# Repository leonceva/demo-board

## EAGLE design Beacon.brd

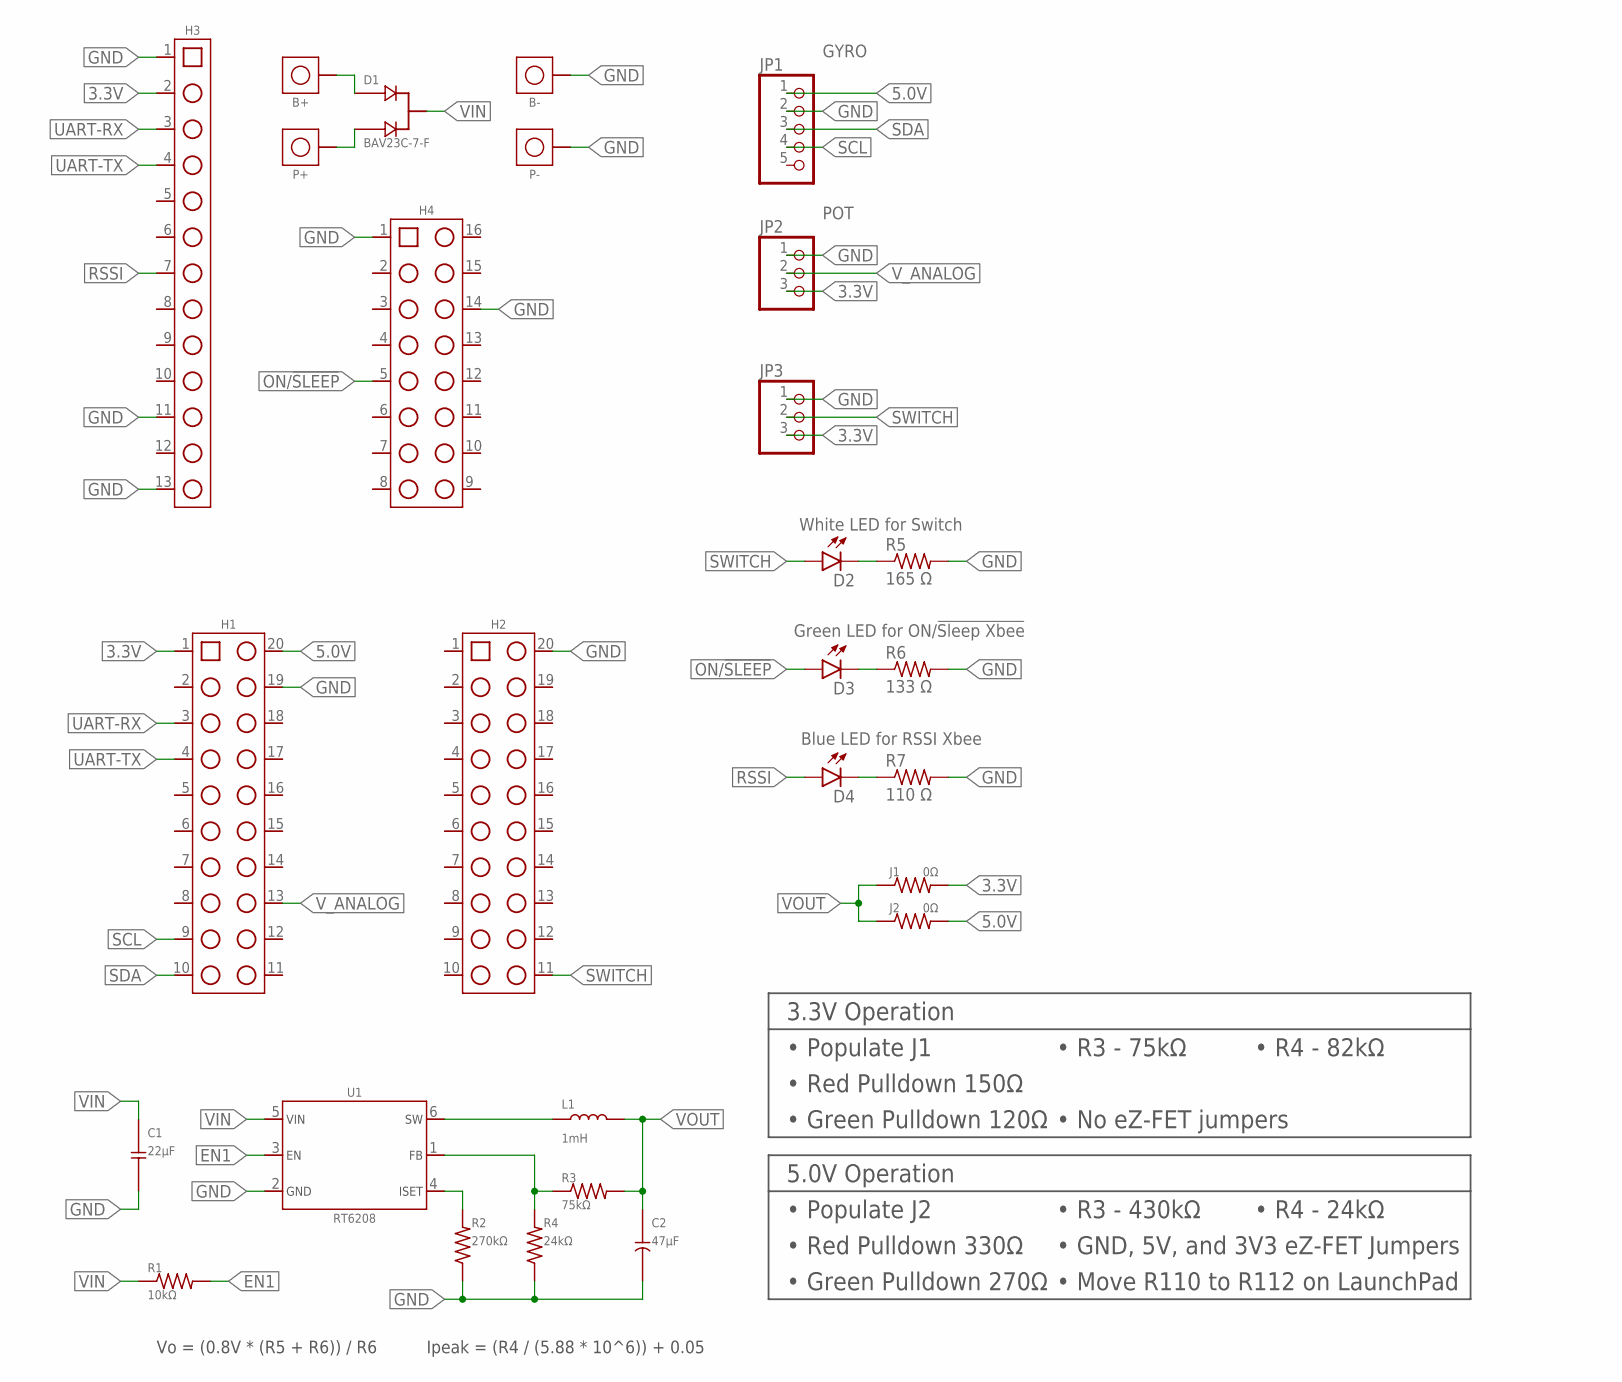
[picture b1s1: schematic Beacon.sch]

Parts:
B+: CON_HEADER-01WTB-24G; THT_WTB-24G
B-: CON_HEADER-01WTB-24G; THT_WTB-24G
C1: 22µF; SMT_1206
C2: 47µF; SMT_CAP-1206
D1: BAV23C-7-F; SMT_SOT23-3
D2, D3, D4: BEAGLEBONE_BLUE_LED-FKIT-1206; BEAGLEBONE_BLUE_BEAGLEBONE_BLUE_FKIT-LED-1206
H1, H2: CON_HEADER-20; CON_HEADER-0.1"-TH-2×10
H3: CON_HEADER-13SM-B; CON_HEADER-2MM-SM-1×13B
H4: CON_HEADER-16SM-B; CON_HEADER-2MM-SM-1×16B
J1, J2: 0Ω; SMT_0603
JP1: PINHD-1X5; 1X05
JP2, JP3: PINHD-1X3/90; 1X03/90
L1: 1mH; SMT_1210
P+: CON_HEADER-01WTB-24G; THT_WTB-24G
P-: CON_HEADER-01WTB-24G; THT_WTB-24G
R1: 10kΩ; SMT_0603
R2: 270kΩ; SMT_0603
R3: 75kΩ; SMT_0603
R4: 24kΩ; SMT_0603
R5: 165 Ω; RES_1206
R6: 133 Ω; RES_1206
R7: 110 Ω; RES_1206
U1: RT6208; SMT_SOT23-6

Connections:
3.3V: H1.1 (PIN_1), H3.2 (PIN_2), J1.2, JP2.3, JP3.3
5.0V: H1.20 (PIN_20), J2.2, JP1.1
EN1: R1.2, U1.3 (B)
FB: R3.1, R4.2, U1.1 (E)
GND: B-.1, C1.1, C2.2, H1.19 (PIN_19), H2.20 (PIN_20), H3.1 (PIN_1), H3.11 (PIN_11), H3.13 (PIN_13), H4.1 (PIN_1), H4.14 (PIN_14), JP1.2, JP2.1, JP3.1, P-.1, R2.1, R4.1, R5.2, R6.2, R7.2, U1.2 (C)
ISET: R2.2, U1.4 (D)
unnamed: D2.C, R5.1
unnamed: D3.C, R6.1
unnamed: D4.C, R7.1
unnamed: B+.1, D1.1 (A1)
unnamed: D1.2 (A2), P+.1
ON/!SLEEP: D3.A, H4.5 (PIN_5)
RSSI: D4.A, H3.7 (PIN_7)
SCL: H1.9 (PIN_9), JP1.4
SDA: H1.10 (PIN_10), JP1.3
SW: L1.1, U1.6 (F)
SWITCH: D2.A, H2.11 (PIN_11), JP3.2
UART-RX: H1.3 (PIN_3), H3.3 (PIN_3)
UART-TX: H1.4 (PIN_4), H3.4 (PIN_4)
VIN: C1.2, D1.3 (CC), R1.1, U1.5 (A)
VOUT: C2.1, J1.1, J2.1, L1.2, R3.2
V_ANALOG: H1.13 (PIN_13), JP2.2

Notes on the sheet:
3.3V Operation
5.0V Operation
• Populate J1
• R4 - 82kΩ
• R3 - 75kΩ
• Red Pulldown 150Ω
• Green Pulldown 120Ω
• Populate J2
• Red Pulldown 330Ω
• Green Pulldown 270Ω
• R3 - 430kΩ
• Move R110 to R112 on LaunchPad
• GND, 5V, and 3V3 eZ-FET Jumpers
Vo = (0.8V * (R5 + R6)) / R6
Ipeak = (R4 / (5.88 * 10^6)) + 0.05
• No eZ-FET jumpers
• R4 - 24kΩ
GYRO
POT
White LED for Switch
Green LED for ON/!Sleep Xbee
Blue LED for RSSI Xbee

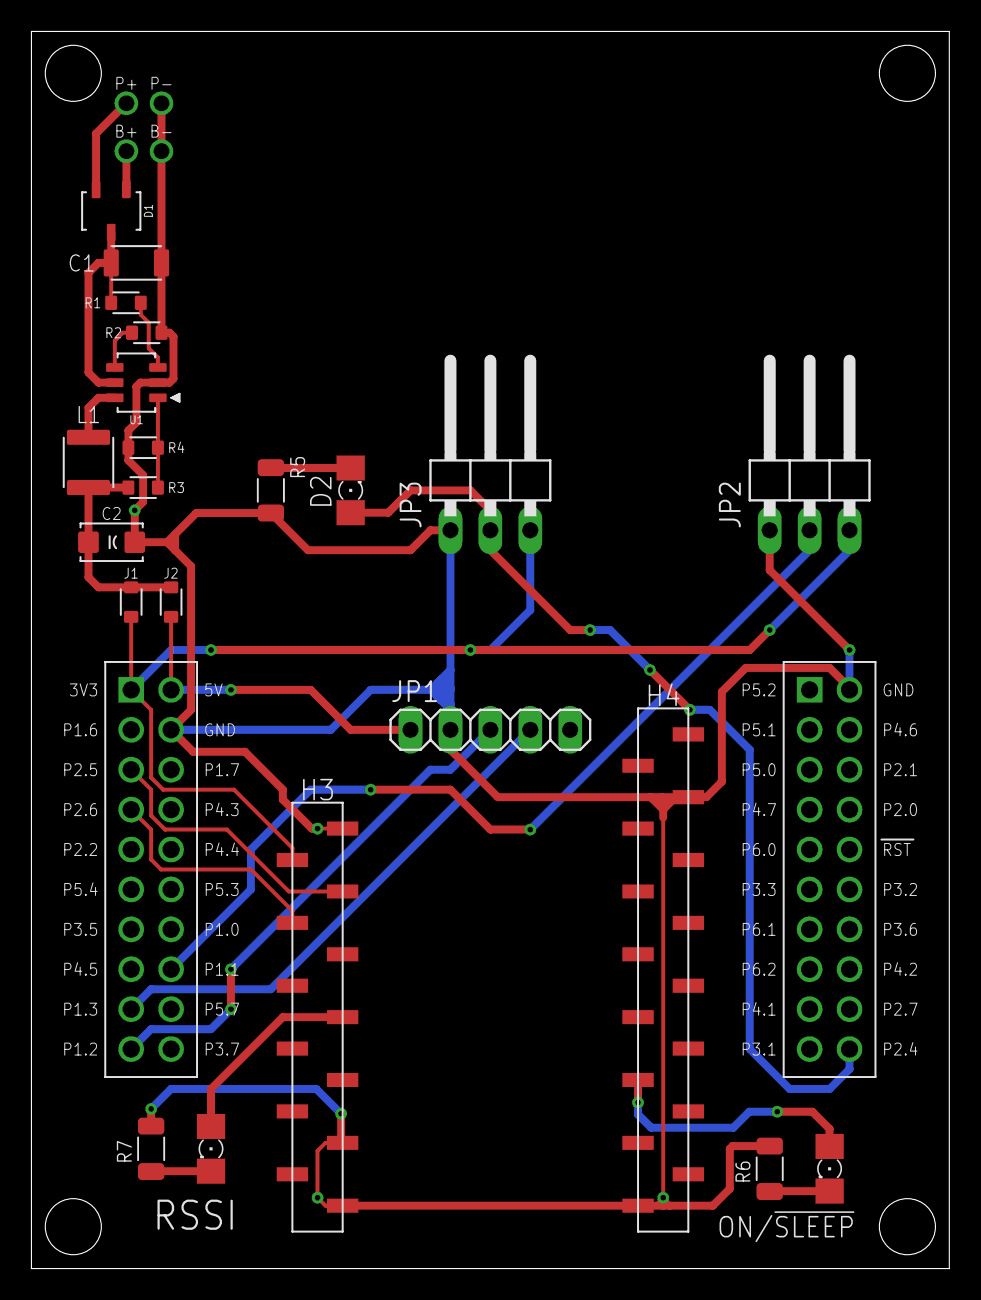
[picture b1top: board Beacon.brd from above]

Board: 2 copper layers, 58.4 x 78.7 mm, 28 parts (0 on the bottom side), 22 nets.

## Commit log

2022-08-25 sensor and xbee working, communication protocol needed
2022-08-26 added command, needs testing
2022-09-29 sending same analogValue fixed
2022-09-29 created demo board class for API, and skeleton for react app
2022-09-30 final
2022-10-04 Added basicn structure and functionality to the ui
2022-10-08 pcb for launchpad shield
2022-10-11 manual mode operational, adding features for automatic mode
2022-10-11 small changes
2022-10-12 fail cases for sensor controller not running, and unable to reach demo-board
2022-10-12 added small animation
2022-10-14 added automatic mode controls
2022-10-18 seems all functional
